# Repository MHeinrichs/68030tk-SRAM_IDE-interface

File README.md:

[This project moved to gitlab on the day M$ bought github](https://gitlab.com/MHeinrichs/68030tk-SRAM_IDE-interface)

The new repository is at: https://gitlab.com/MHeinrichs/68030tk-SRAM_IDE-interface

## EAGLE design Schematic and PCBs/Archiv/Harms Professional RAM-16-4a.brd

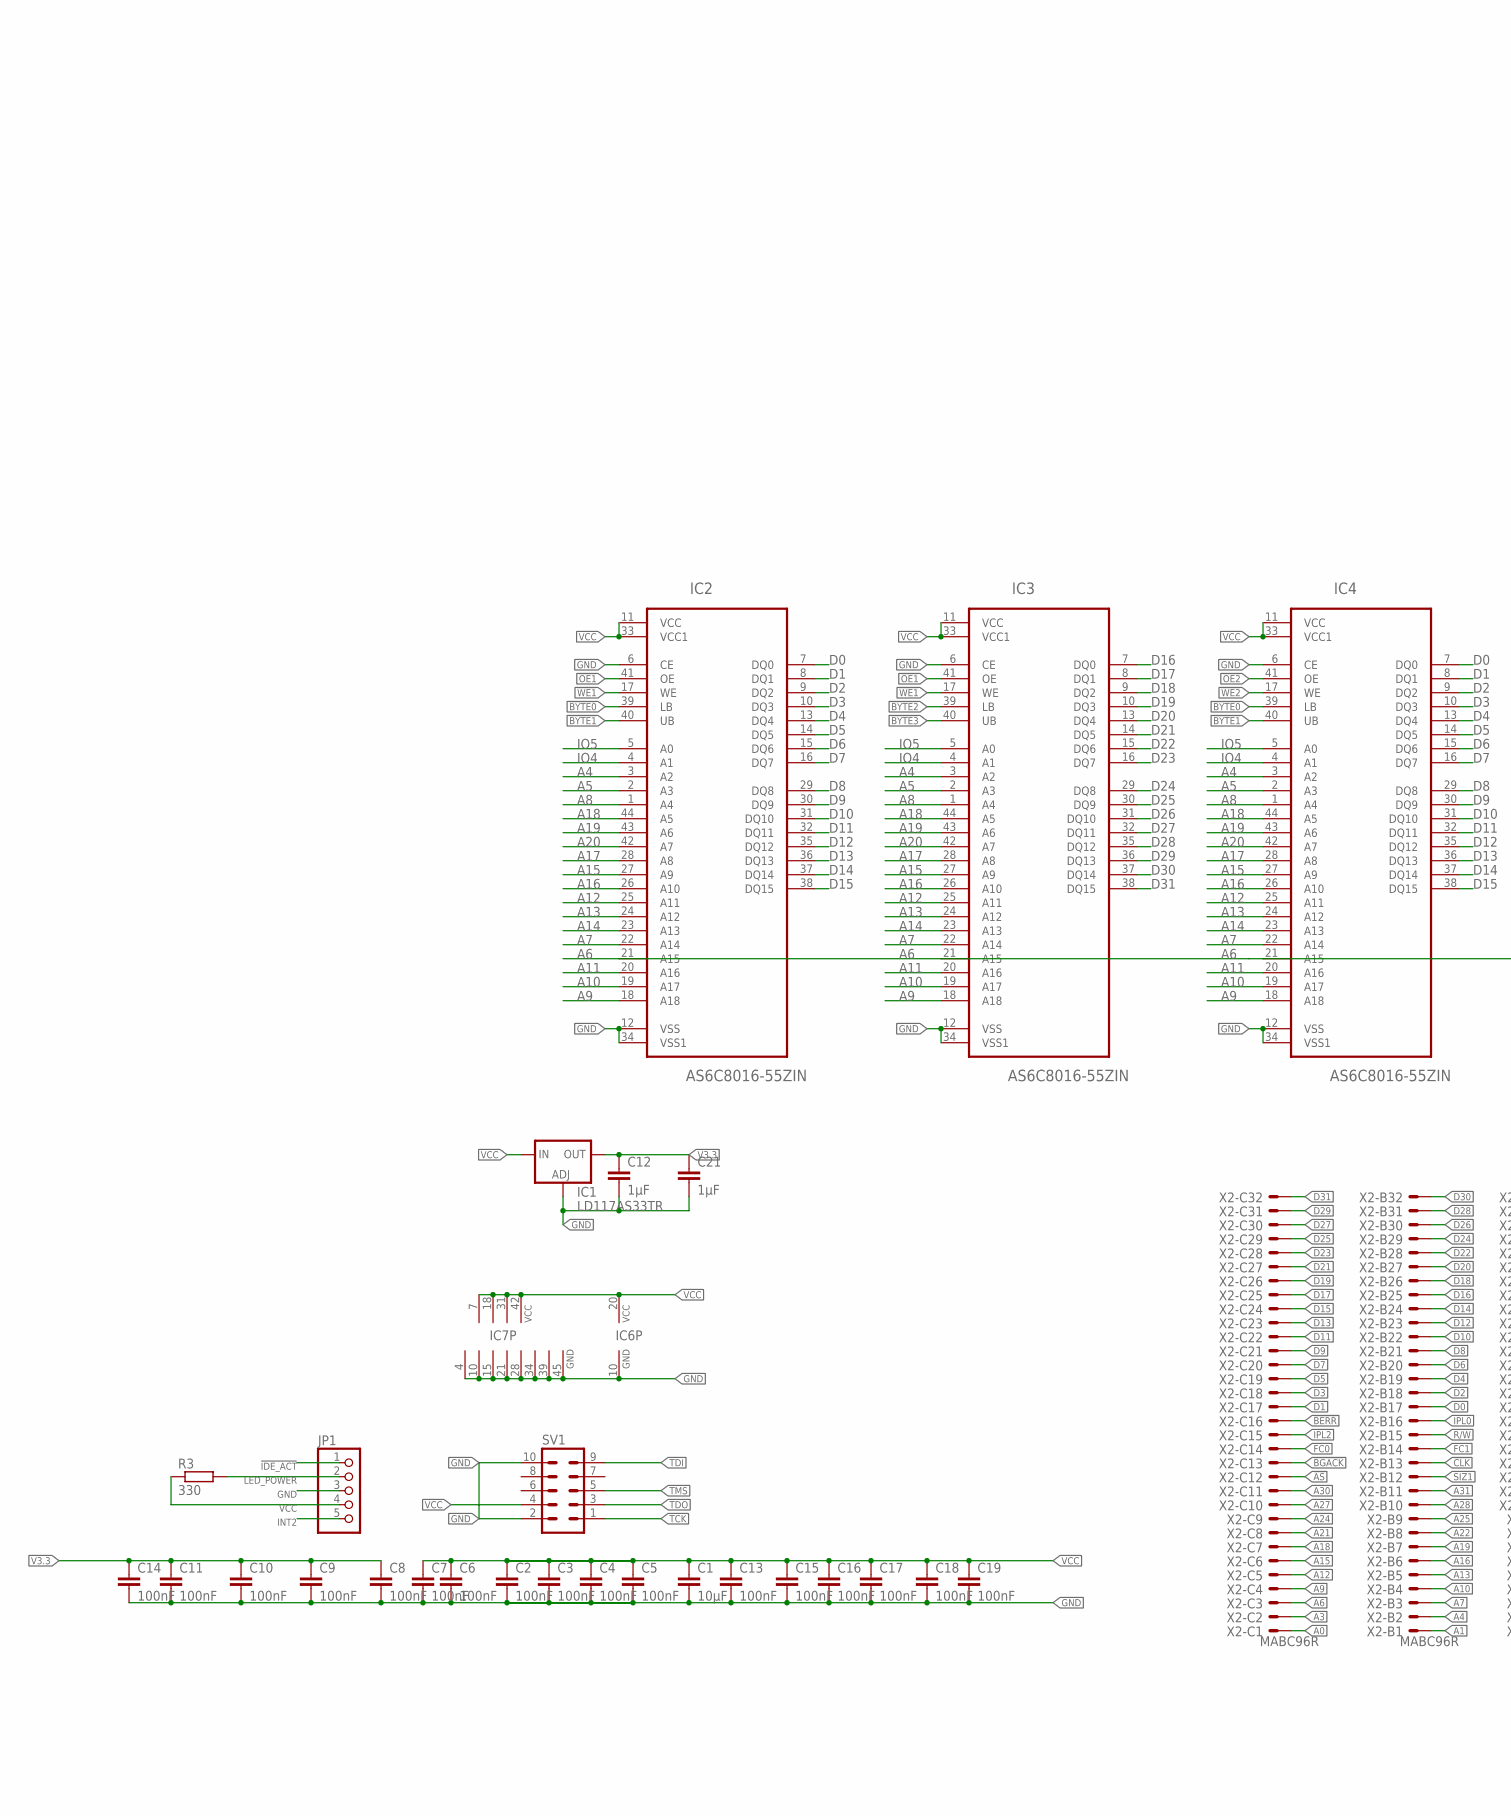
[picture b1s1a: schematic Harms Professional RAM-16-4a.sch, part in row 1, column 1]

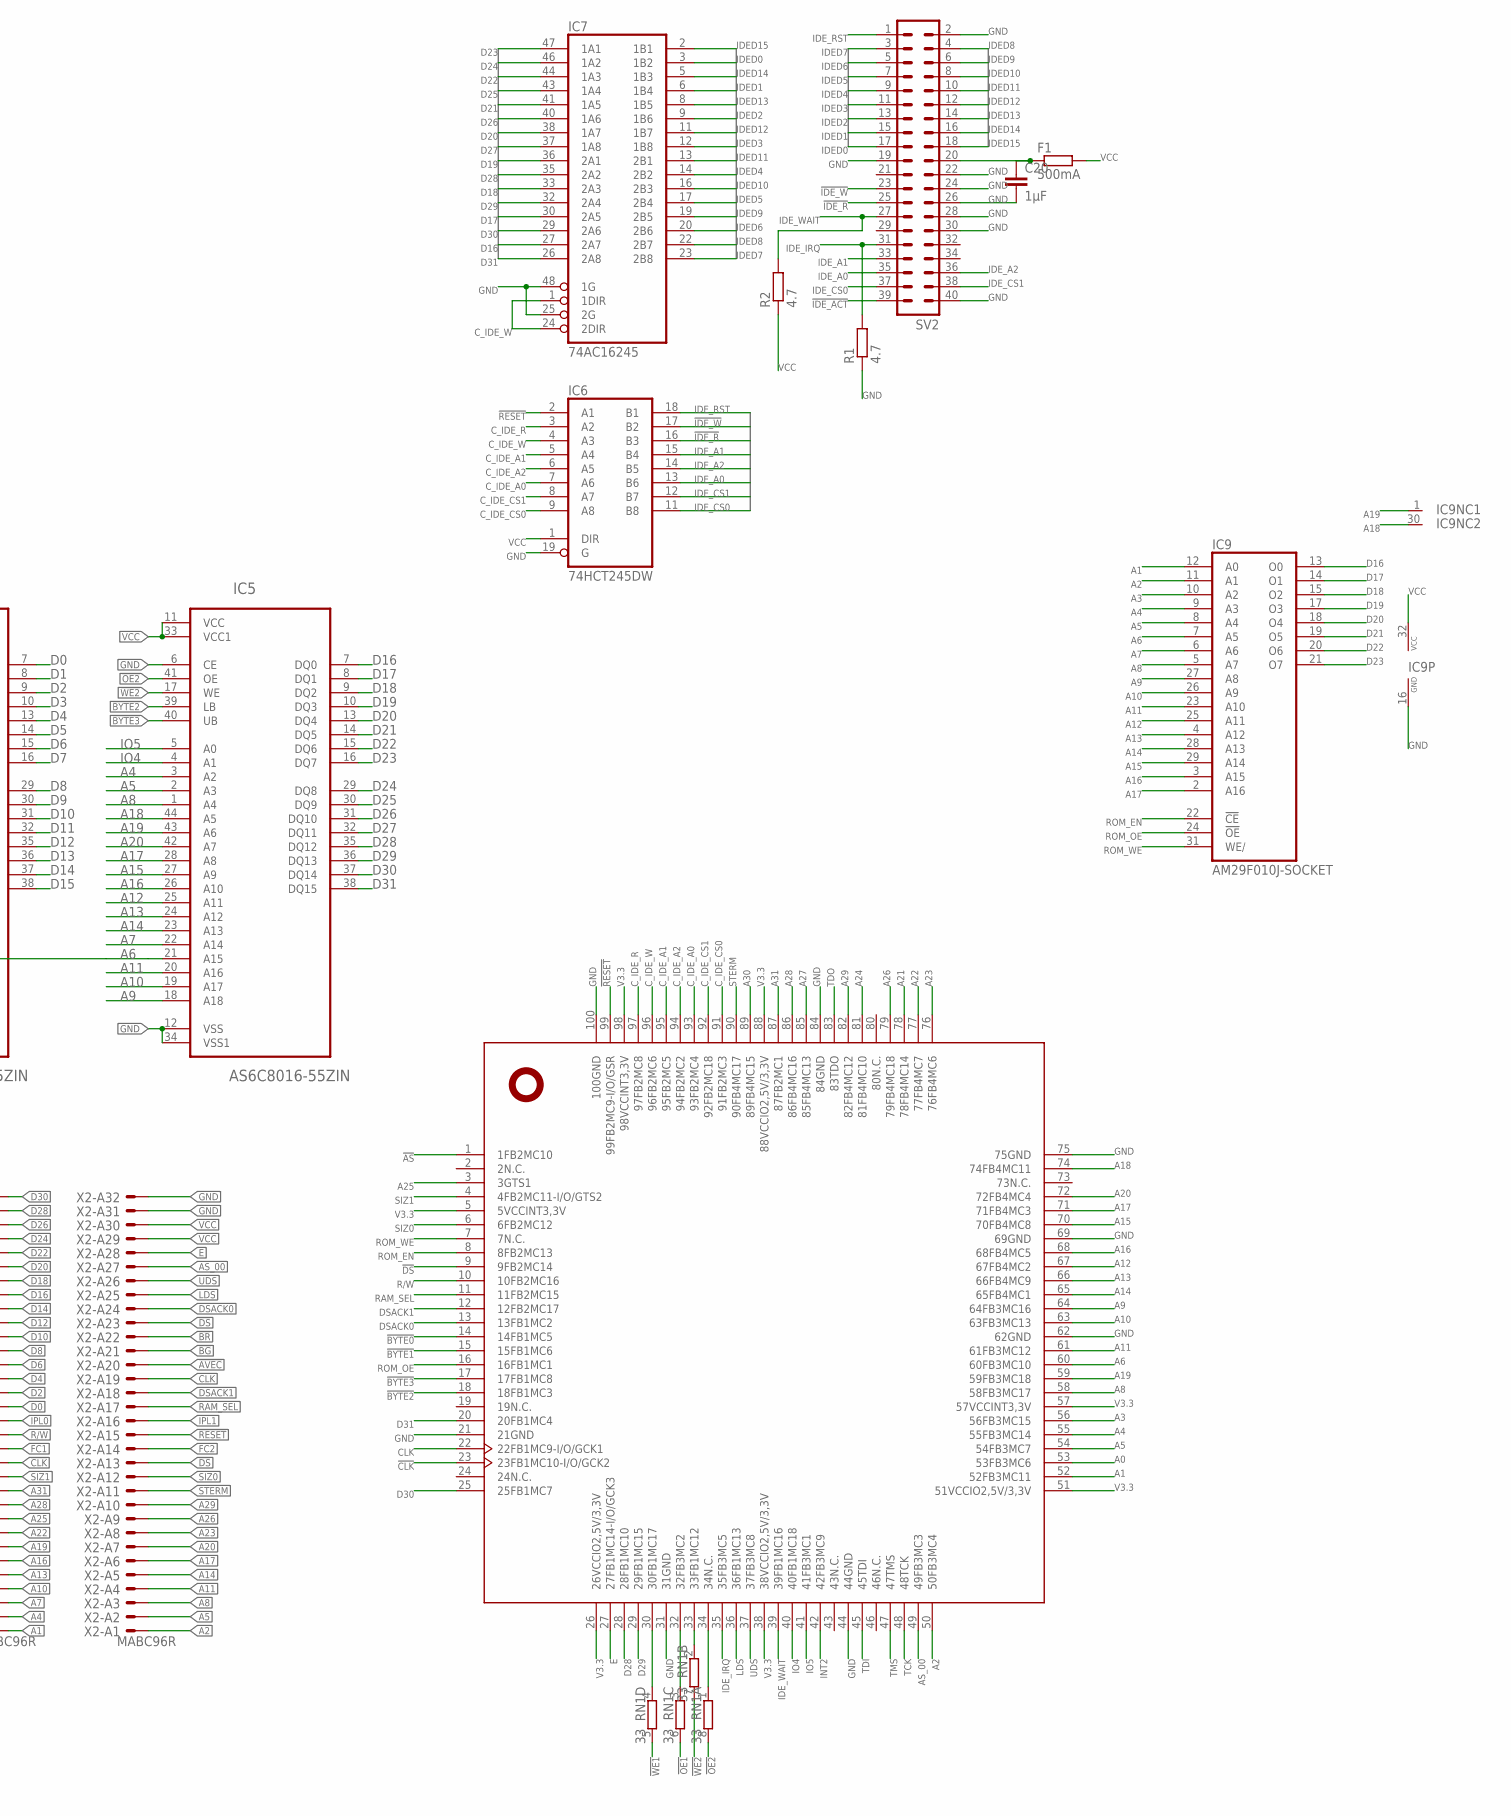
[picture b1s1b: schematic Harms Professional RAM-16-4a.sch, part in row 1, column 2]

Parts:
C1: 10µF; C0805K
C2, C3, C4, C5, C6, C7, C8, C9, C10, C11, C13, C14, C15, C16, C17, C18, C19: 100nF; C0603K
C12, C20, C21: 1µF; C0805K
F1: 500mA; R2512
IC1: LD117AS33TR; SOT223
IC2, IC3, IC4, IC5: AS6C8016-55ZIN; TSOP-2_44
IC6: 74HCT245DW; SO20W
IC7: 74AC16245; SSOP48DL
IC9: AM29F010J-SOCKET; PLCC-32-SMT-TT
IC10: XC9572XLTQ100; TQ100
JP1: PINHD-1X5; 1X05
R1, R2: 4.7; R0603
R3: 330; R0603
RN1: 33; CAY16
SV1: ML10
SV2: ML40
X2: MABC96R

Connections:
!AS: IC10.1 (1FB2MC10), X2.C12
!AVEC: X2.A20
!BERR: X2.C16
!BG: X2.A21
!BGACK: X2.C13
!BR: X2.A22
!BYTE0: IC2.39 (LB), IC4.39 (LB), IC10.14 (14FB1MC5)
!BYTE1: IC2.40 (UB), IC4.40 (UB), IC10.15 (15FB1MC6)
!BYTE2: IC3.39 (LB), IC5.39 (LB), IC10.18 (18FB1MC3)
!BYTE3: IC3.40 (UB), IC5.40 (UB), IC10.17 (17FB1MC8)
!CLK: IC10.23 (23FB1MC10-I/O/GCK2), X2.B13
!DS: IC10.9 (9FB2MC14), X2.A13, X2.A23
!IDE_ACT: JP1.1, SV2.39
!IDE_R: IC6.16 (B3), SV2.25
!IDE_W: IC6.17 (B2), SV2.23
!OE1: IC2.41 (OE), IC3.41 (OE), RN1.6 (2)
!OE2: IC4.41 (OE), IC5.41 (OE), RN1.8 (2)
!RESET: IC6.2 (A1), IC10.99 (99FB2MC9-I/O/GSR), X2.A15
!WE1: IC2.17 (WE), IC3.17 (WE), RN1.5 (2)
!WE2: IC4.17 (WE), IC5.17 (WE), RN1.7 (2)
A0: IC10.53 (53FB3MC6), X2.C1
A1: IC9.12 (A0), IC10.52 (52FB3MC11), X2.B1
A2: IC9.11 (A1), IC10.50 (50FB3MC4), X2.A1
A3: IC9.10 (A2), IC10.56 (56FB3MC15), X2.C2
A4: IC2.3 (A2), IC3.3 (A2), IC4.3 (A2), IC5.3 (A2), IC9.9 (A3), IC10.55 (55FB3MC14), X2.B2
A5: IC2.2 (A3), IC3.2 (A3), IC4.2 (A3), IC5.2 (A3), IC9.8 (A4), IC10.54 (54FB3MC7), X2.A2
A6: IC2.21 (A15), IC3.21 (A15), IC4.21 (A15), IC5.21 (A15), IC9.7 (A5), IC10.60 (60FB3MC10), X2.C3
A7: IC2.22 (A14), IC3.22 (A14), IC4.22 (A14), IC5.22 (A14), IC9.6 (A6), X2.B3
A8: IC2.1 (A4), IC3.1 (A4), IC4.1 (A4), IC5.1 (A4), IC9.5 (A7), IC10.58 (58FB3MC17), X2.A3
A9: IC2.18 (A18), IC3.18 (A18), IC4.18 (A18), IC5.18 (A18), IC9.27 (A8), IC10.64 (64FB3MC16), X2.C4
A10: IC2.19 (A17), IC3.19 (A17), IC4.19 (A17), IC5.19 (A17), IC9.26 (A9), IC10.63 (63FB3MC13), X2.B4
A11: IC2.20 (A16), IC3.20 (A16), IC4.20 (A16), IC5.20 (A16), IC9.23 (A10), IC10.61 (61FB3MC12), X2.A4
A12: IC2.25 (A11), IC3.25 (A11), IC4.25 (A11), IC5.25 (A11), IC9.25 (A11), IC10.67 (67FB4MC2), X2.C5
A13: IC2.24 (A12), IC3.24 (A12), IC4.24 (A12), IC5.24 (A12), IC9.4 (A12), IC10.66 (66FB4MC9), X2.B5
A14: IC2.23 (A13), IC3.23 (A13), IC4.23 (A13), IC5.23 (A13), IC9.28 (A13), IC10.65 (65FB4MC1), X2.A5
A15: IC2.27 (A9), IC3.27 (A9), IC4.27 (A9), IC5.27 (A9), IC9.29 (A14), IC10.70 (70FB4MC8), X2.C6
A16: IC2.26 (A10), IC3.26 (A10), IC4.26 (A10), IC5.26 (A10), IC9.3 (A15), IC10.68 (68FB4MC5), X2.B6
A17: IC2.28 (A8), IC3.28 (A8), IC4.28 (A8), IC5.28 (A8), IC9.2 (A16), IC10.71 (71FB4MC3), X2.A6
A18: IC2.44 (A5), IC3.44 (A5), IC4.44 (A5), IC5.44 (A5), IC9.30 (NC), IC10.74 (74FB4MC11), X2.C7
A19: IC2.43 (A6), IC3.43 (A6), IC4.43 (A6), IC5.43 (A6), IC9.1 (NC), IC10.59 (59FB3MC18), X2.B7
A20: IC2.42 (A7), IC3.42 (A7), IC4.42 (A7), IC5.42 (A7), IC10.72 (72FB4MC4), X2.A7
A21: IC10.78 (78FB4MC14), X2.C8
A22: IC10.77 (77FB4MC7), X2.B8
A23: IC10.76 (76FB4MC6), X2.A8
A24: IC10.81 (81FB4MC10), X2.C9
A25: IC10.3 (3GTS1), X2.B9
A26: IC10.79 (79FB4MC18), X2.A9
A27: IC10.85 (85FB4MC13), X2.C10
A28: IC10.86 (86FB4MC16), X2.B10
A29: IC10.82 (82FB4MC12), X2.A10
A30: IC10.89 (89FB4MC15), X2.C11
A31: IC10.87 (87FB2MC1), X2.B11
AS_00: IC10.49 (49FB3MC3), X2.A27
CLK: IC10.22 (22FB1MC9-I/O/GCK1), X2.A19
C_IDE_A0: IC6.7 (A6), IC10.93 (93FB2MC4)
C_IDE_A1: IC6.5 (A4), IC10.95 (95FB2MC5)
C_IDE_A2: IC6.6 (A5), IC10.94 (94FB2MC2)
C_IDE_CS0: IC6.9 (A8), IC10.91 (91FB2MC3)
C_IDE_CS1: IC6.8 (A7), IC10.92 (92FB2MC18)
C_IDE_R: IC6.3 (A2), IC10.97 (97FB2MC8)
C_IDE_W: IC6.4 (A3), IC7.1 (1DIR), IC7.24 (2DIR), IC10.96 (96FB2MC6)
D0: IC2.7 (DQ0), IC4.7 (DQ0), X2.B17
D1: IC2.8 (DQ1), IC4.8 (DQ1), X2.C17
D2: IC2.9 (DQ2), IC4.9 (DQ2), X2.B18
D3: IC2.10 (DQ3), IC4.10 (DQ3), X2.C18
D4: IC2.13 (DQ4), IC4.13 (DQ4), X2.B19
D5: IC2.14 (DQ5), IC4.14 (DQ5), X2.C19
D6: IC2.15 (DQ6), IC4.15 (DQ6), X2.B20
D7: IC2.16 (DQ7), IC4.16 (DQ7), X2.C20
D8: IC2.29 (DQ8), IC4.29 (DQ8), X2.B21
D9: IC2.30 (DQ9), IC4.30 (DQ9), X2.C21
D10: IC2.31 (DQ10), IC4.31 (DQ10), X2.B22
D11: IC2.32 (DQ11), IC4.32 (DQ11), X2.C22
D12: IC2.35 (DQ12), IC4.35 (DQ12), X2.B23
D13: IC2.36 (DQ13), IC4.36 (DQ13), X2.C23
D14: IC2.37 (DQ14), IC4.37 (DQ14), X2.B24
D15: IC2.38 (DQ15), IC4.38 (DQ15), X2.C24
D16: IC3.7 (DQ0), IC5.7 (DQ0), IC7.27 (2A7), IC9.13 (O0), X2.B25
D17: IC3.8 (DQ1), IC5.8 (DQ1), IC7.30 (2A5), IC9.14 (O1), X2.C25
D18: IC3.9 (DQ2), IC5.9 (DQ2), IC7.33 (2A3), IC9.15 (O2), X2.B26
D19: IC3.10 (DQ3), IC5.10 (DQ3), IC7.36 (2A1), IC9.17 (O3), X2.C26
D20: IC3.13 (DQ4), IC5.13 (DQ4), IC7.38 (1A7), IC9.18 (O4), X2.B27
D21: IC3.14 (DQ5), IC5.14 (DQ5), IC7.41 (1A5), IC9.19 (O5), X2.C27
D22: IC3.15 (DQ6), IC5.15 (DQ6), IC7.44 (1A3), IC9.20 (O6), X2.B28
D23: IC3.16 (DQ7), IC5.16 (DQ7), IC7.47 (1A1), IC9.21 (O7), X2.C28
D24: IC3.29 (DQ8), IC5.29 (DQ8), IC7.46 (1A2), X2.B29
D25: IC3.30 (DQ9), IC5.30 (DQ9), IC7.43 (1A4), X2.C29
D26: IC3.31 (DQ10), IC5.31 (DQ10), IC7.40 (1A6), X2.B30
D27: IC3.32 (DQ11), IC5.32 (DQ11), IC7.37 (1A8), X2.C30
D28: IC3.35 (DQ12), IC5.35 (DQ12), IC7.35 (2A2), IC10.28 (28FB1MC10), X2.B31
D29: IC3.36 (DQ13), IC5.36 (DQ13), IC7.32 (2A4), IC10.29 (29FB1MC15), X2.C31
D30: IC3.37 (DQ14), IC5.37 (DQ14), IC7.29 (2A6), IC10.25 (25FB1MC7), X2.B32
D31: IC3.38 (DQ15), IC5.38 (DQ15), IC7.26 (2A8), IC10.20 (20FB1MC4), X2.C32
DSACK0: IC10.13 (13FB1MC2), X2.A24
DSACK1: IC10.12 (12FB2MC17), X2.A18
E: IC10.27 (27FB1MC14-I/O/GCK3), X2.A28
FC0: X2.C14
FC1: X2.B14
FC2: X2.A14
GND: C1.2, C2.2, C3.2, C4.2, C5.2, C6.2, C7.2, C8.2, C9.2, C10.2, C11.2, C12.2, C13.2, C14.2, C15.2, C16.2, C17.2, C18.2, C19.2, C20.2, C21.2, IC1.1 (ADJ), IC2.6 (CE), IC2.12 (VSS), IC2.34 (VSS1), IC3.6 (CE), IC3.12 (VSS), IC3.34 (VSS1), IC4.6 (CE), IC4.12 (VSS), IC4.34 (VSS1), IC5.6 (CE), IC5.12 (VSS), IC5.34 (VSS1), IC6.10 (GND), IC6.19 (G), IC7.4 (GND), IC7.10 (GND), IC7.15 (GND), IC7.21 (GND), IC7.25 (2G), IC7.28 (GND), IC7.34 (GND), IC7.39 (GND), IC7.45 (GND), IC7.48 (1G), IC9.16 (GND), IC10.21 (21GND), IC10.31 (31GND), IC10.44 (44GND), IC10.62 (62GND), IC10.69 (69GND), IC10.75 (75GND), IC10.84 (84GND), IC10.100 (100GND), JP1.3, R1.1, SV1.2, SV1.10, SV2.2, SV2.19, SV2.22, SV2.24, SV2.26, SV2.28, SV2.30, SV2.40, X2.A31, X2.A32
IDED0: IC7.3 (1B2), SV2.17
IDED1: IC7.6 (1B4), SV2.15
IDED2: IC7.9 (1B6), SV2.13
IDED3: IC7.12 (1B8), SV2.11
IDED4: IC7.14 (2B2), SV2.9
IDED5: IC7.17 (2B4), SV2.7
IDED6: IC7.20 (2B6), SV2.5
IDED7: IC7.23 (2B8), SV2.3
IDED8: IC7.22 (2B7), SV2.4
IDED9: IC7.19 (2B5), SV2.6
IDED10: IC7.16 (2B3), SV2.8
IDED11: IC7.13 (2B1), SV2.10
IDED12: IC7.11 (1B7), SV2.12
IDED13: IC7.8 (1B5), SV2.14
IDED14: IC7.5 (1B3), SV2.16
IDED15: IC7.2 (1B1), SV2.18
IDE_A0: IC6.13 (B6), SV2.35
IDE_A1: IC6.15 (B4), SV2.33
IDE_A2: IC6.14 (B5), SV2.36
IDE_CS0: IC6.11 (B8), SV2.37
IDE_CS1: IC6.12 (B7), SV2.38
IDE_IRQ: IC10.35 (35FB3MC5), R1.2, SV2.31
IDE_RST: IC6.18 (B1), SV2.1
IDE_WAIT: IC10.39 (39FB1MC16), R2.2, SV2.27
INT2: IC10.42 (42FB3MC9), JP1.5
IO4: IC2.4 (A1), IC3.4 (A1), IC4.4 (A1), IC5.4 (A1), IC10.40 (40FB1MC18)
IO5: IC2.5 (A0), IC3.5 (A0), IC4.5 (A0), IC5.5 (A0), IC10.41 (41FB3MC1)
IPL0: X2.B16
IPL1: X2.A16
IPL2: X2.C15
KEY_PIN_POWER: C20.1, F1.1, SV2.20
LDS: IC10.36 (36FB1MC13), X2.A25
LED_POWER: JP1.2, R3.2
unnamed: IC10.30 (30FB1MC17), RN1.4 (1)
unnamed: IC10.34 (34N.C.), RN1.1
unnamed: IC10.33 (33FB1MC12), RN1.2 (1)
unnamed: IC10.32 (32FB3MC2), RN1.3 (1)
R/W: IC10.10 (10FB2MC16), X2.B15
RAM_SEL: IC10.11 (11FB2MC15), X2.A17
ROM_EN: IC9.22 (!CE), IC10.8 (8FB2MC13)
ROM_OE: IC9.24 (!OE), IC10.16 (16FB1MC1)
ROM_WE: IC9.31 (WE/), IC10.7 (7N.C.)
SIZ0: IC10.6 (6FB2MC12), X2.A12
SIZ1: IC10.4 (4FB2MC11-I/O/GTS2), X2.B12
STERM: IC10.90 (90FB4MC17), X2.A11
TCK: IC10.48 (48TCK), SV1.1
TDI: IC10.45 (45TDI), SV1.9
TDO: IC10.83 (83TDO), SV1.3
TMS: IC10.47 (47TMS), SV1.5
UDS: IC10.37 (37FB3MC8), X2.A26
V3.3: C8.1, C9.1, C10.1, C11.1, C12.1, C14.1, C21.1, IC1.4 (OUT), IC10.5 (5VCCINT3,3V), IC10.26 (26VCCIO2,5V/3,3V), IC10.38 (38VCCIO2,5V/3,3V), IC10.51 (51VCCIO2,5V/3,3V), IC10.57 (57VCCINT3,3V), IC10.88 (88VCCIO2,5V/3,3V), IC10.98 (98VCCINT3,3V)
VCC: C1.1, C2.1, C3.1, C4.1, C5.1, C6.1, C7.1, C13.1, C15.1, C16.1, C17.1, C18.1, C19.1, F1.2, IC1.3 (IN), IC2.11 (VCC), IC2.33 (VCC1), IC3.11 (VCC), IC3.33 (VCC1), IC4.11 (VCC), IC4.33 (VCC1), IC5.11 (VCC), IC5.33 (VCC1), IC6.1 (DIR), IC6.20 (VCC), IC7.7 (VCC), IC7.18 (VCC), IC7.31 (VCC), IC7.42 (VCC), IC9.32 (VCC), JP1.4, R2.1, R3.1, SV1.4, X2.A29, X2.A30

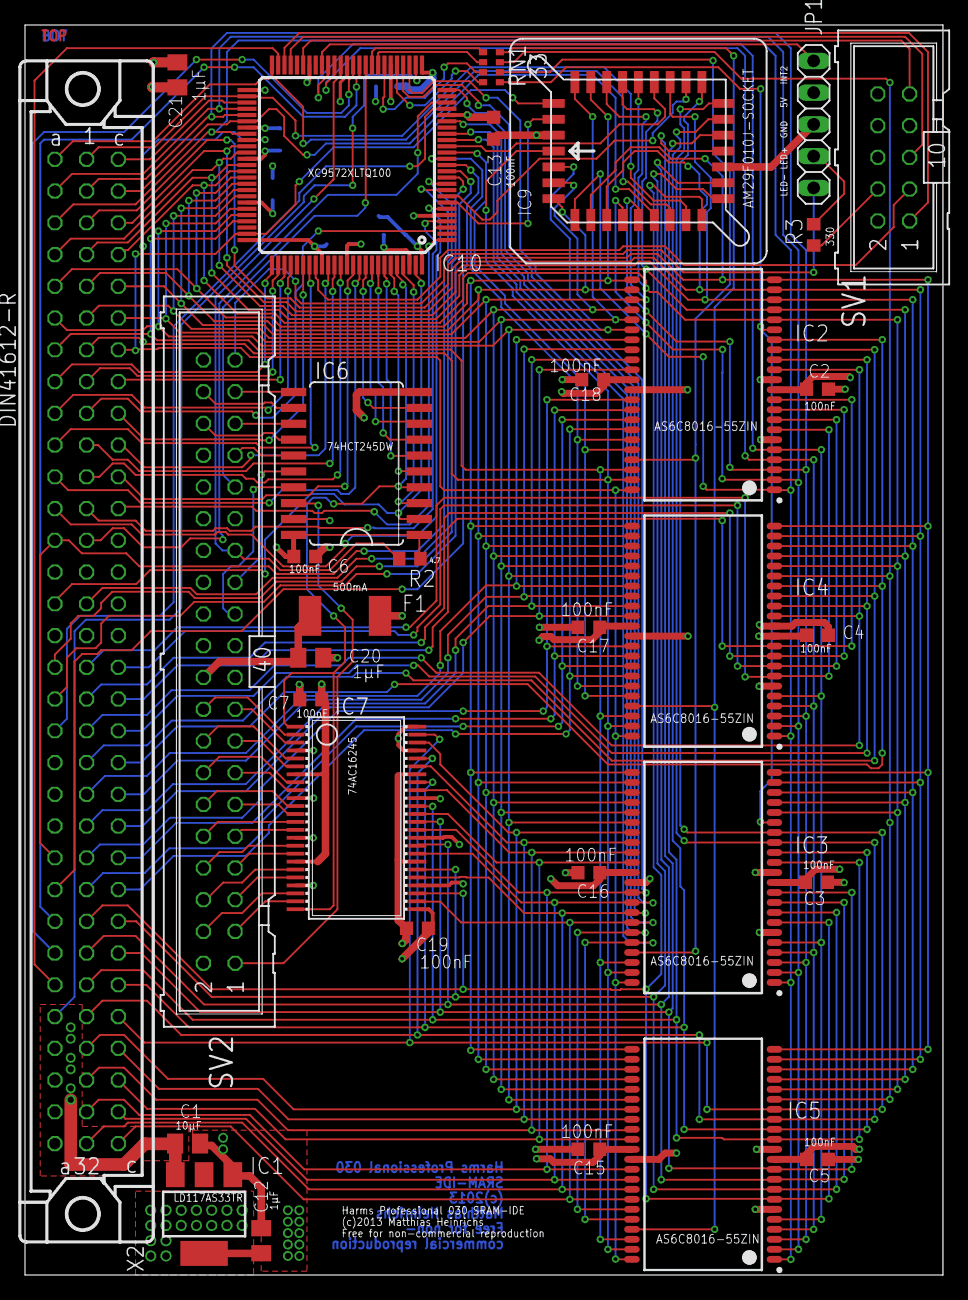
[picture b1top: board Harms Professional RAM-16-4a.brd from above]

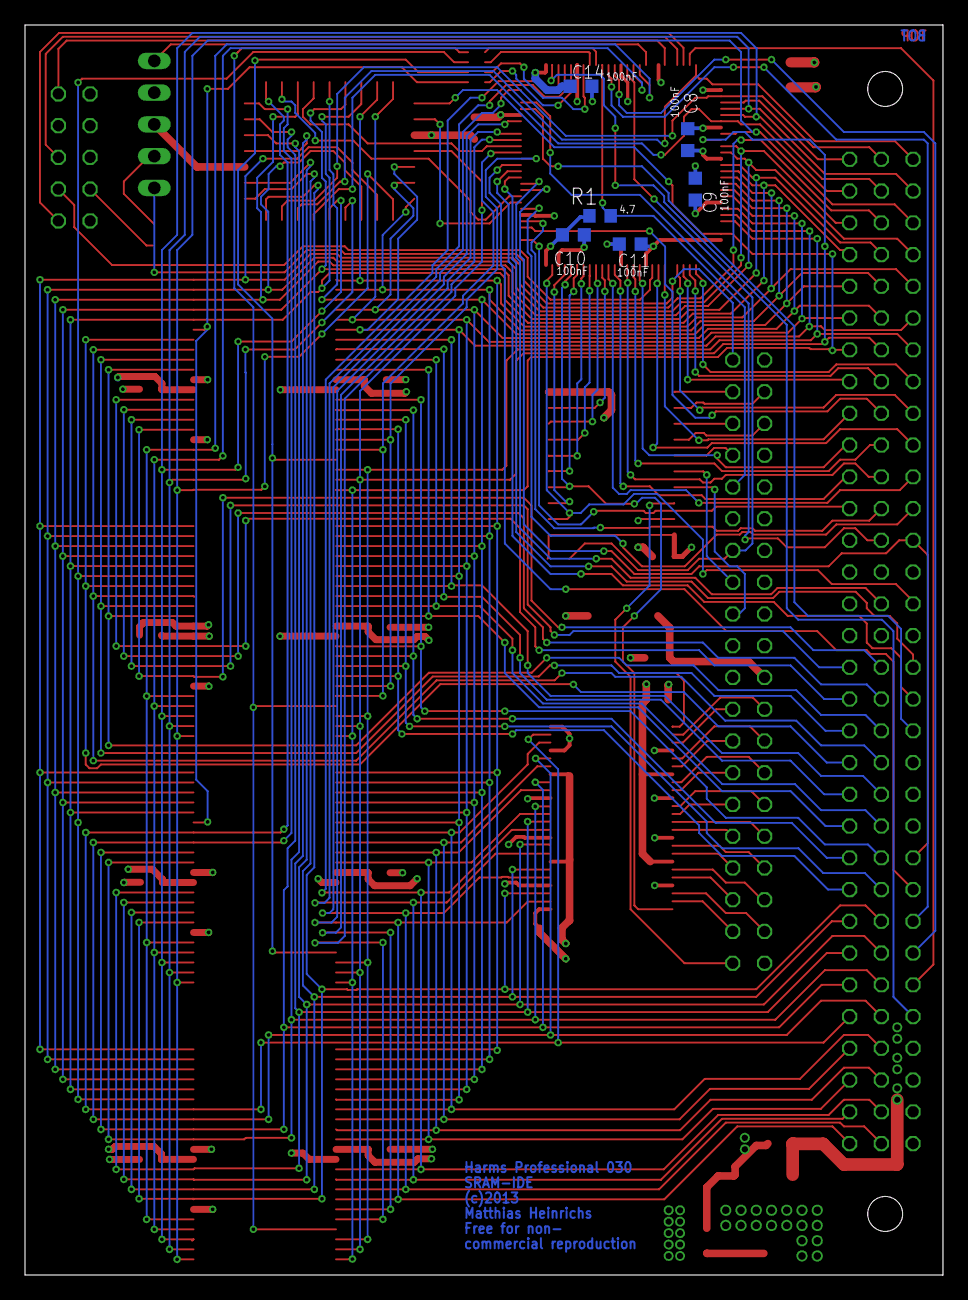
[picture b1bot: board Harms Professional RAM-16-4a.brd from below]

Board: 4 copper layers, 73.4 x 100.0 mm, 39 parts (6 on the bottom side), 141 nets.

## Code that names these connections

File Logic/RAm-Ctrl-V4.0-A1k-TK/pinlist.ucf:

#PIN MAP for the Harms Professional RAM Controller
NET reset LOC = "P99";
NET "IDE_W" LOC = "P97";
NET "IDE_R" LOC = "P96";
NET "IDE_A[1]" LOC = "P95";
NET "IDE_A[2]" LOC = "P94";
NET "IDE_A[0]" LOC = "P93";
NET "IDE_CS[1]" LOC = "P92";
NET "IDE_CS[0]" LOC = "P91";
NET "STERM" LOC = "P90";
NET "A[30]" LOC = "P89";
NET "A[31]" LOC = "P87";
NET "A[28]" LOC = "P86";
NET "A[27]" LOC = "P85";
NET "A[29]" LOC = "P82";
NET "A[24]" LOC = "P81";
NET "A[26]" LOC = "P79";
NET "A[21]" LOC = "P78";
NET "A[22]" LOC = "P77";
NET "A[23]" LOC = "P76";
NET "A[18]" LOC = "P74";
NET "A[20]" LOC = "P72";
NET "A[17]" LOC = "P71";
NET "A[15]" LOC = "P70";
NET "A[16]" LOC = "P68";
NET "A[12]" LOC = "P67";
NET "A[13]" LOC = "P66";
NET "A[14]" LOC = "P65";
NET "A[9]" LOC = "P64";
NET "A[10]" LOC = "P63";
NET "A[11]" LOC = "P61";
NET "A[6]" LOC = "P60";
NET "A[19]" LOC = "P59";
NET "A[8]" LOC = "P58";
NET "A[3]" LOC = "P56";
NET "A[4]" LOC = "P55";
NET "A[5]" LOC = "P54";
NET "A[0]" LOC = "P53";
NET "A[1]" LOC = "P52";
NET "A[2]" LOC = "P50";
NET "CIIN" LOC = "P49"; #this is AS_00 on the original HARMS-Board
NET "INT2" LOC = "P42";
NET "IO5" LOC = "P41";
NET "IO4" LOC = "P40";
NET "IDE_WAIT" LOC = "P39";
#NET "UDS" LOC = "P37";
#NET "LDS" LOC = "P36";
NET "IDE_IRQ" LOC = "P35";
NET "OE[1]" LOC = "P34";
NET "WE[1]" LOC = "P33";
NET "OE[0]" LOC = "P32";
NET "WE[0]" LOC = "P30";
NET "D[1]" LOC = "P29"; #Internal D1=external D29
NET "D[0]" LOC = "P28"; #Internal D0=external D28
#NET "E" LOC = "P27";
NET "D[2]" LOC = "P25"; #Internal D2=external D30
NET "ECS" LOC = "P23";
NET "clk" LOC = "P22";
NET "D[3]" LOC = "P20"; #Internal D3=external D31
NET "BYTE[2]" LOC = "P18";
NET "BYTE[3]" LOC = "P17";
NET "ROM_OE" LOC = "P16";
NET "BYTE[1]" LOC = "P15";
NET "BYTE[0]" LOC = "P14";
NET "DSACK[0]" LOC = "P13";
NET "DSACK[1]" LOC = "P12";
NET "nRAM_SEL" LOC = "P11";
NET "RW" LOC = "P10";
NET "nDS" LOC = "P9";
NET "ROM_EN" LOC = "P8";
NET "ROM_WE" LOC = "P7";
NET "SIZ[0]" LOC = "P6";
NET "SIZ[1]" LOC = "P4";
NET "A[25]" LOC = "P3";
NET "IDE_DIR" LOC = "P2";
NET "nAS" LOC = "P1";
#Created by Constraints Editor (xc95144xl-tq100-10) - 2015/02/08
NET "clk" TNM_NET = clk;
TIMESPEC TS_clk = PERIOD "clk" 50 MHz HIGH 50% INPUT_JITTER 100 ps;
#>DISABLED<#OFFSET = IN 2 ns VALID 10 ns BEFORE "clk" RISING;
#>DISABLED<#OFFSET = IN 2 ns VALID 10 ns BEFORE "clk" FALLING;
#Created by Constraints Editor (xc95144xl-tq100-10) - 2015/02/08
INST "A<0>" TNM = ADR;
INST "A<1>" TNM = ADR;
INST "A<2>" TNM = ADR;
INST "A<3>" TNM = ADR;
INST "A<4>" TNM = ADR;
INST "A<5>" TNM = ADR;
INST "A<6>" TNM = ADR;
INST "A<8>" TNM = ADR;
INST "A<9>" TNM = ADR;
INST "A<10>" TNM = ADR;
INST "A<11>" TNM = ADR;
INST "A<12>" TNM = ADR;
INST "A<13>" TNM = ADR;
INST "A<14>" TNM = ADR;
INST "A<15>" TNM = ADR;
INST "A<16>" TNM = ADR;
INST "A<17>" TNM = ADR;
INST "A<18>" TNM = ADR;
INST "A<19>" TNM = ADR;
INST "A<20>" TNM = ADR;
INST "A<21>" TNM = ADR;
INST "A<22>" TNM = ADR;
INST "A<23>" TNM = ADR;
INST "A<24>" TNM = ADR;
INST "A<25>" TNM = ADR;
INST "A<26>" TNM = ADR;
INST "A<27>" TNM = ADR;
INST "A<28>" TNM = ADR;
INST "A<29>" TNM = ADR;
INST "A<30>" TNM = ADR;
INST "A<31>" TNM = ADR;
INST "D<0>" TNM = DATA;
INST "D<1>" TNM = DATA;
INST "D<2>" TNM = DATA;
INST "D<3>" TNM = DATA;
#>DISABLED<#TIMEGRP "DATA" OFFSET = IN 14 ns VALID 20 ns BEFORE "clk" RISING;
INST "nAS" TNM = STROBES;
INST "nDS" TNM = STROBES;
INST "nAS" TNM = STROBES;
INST "nDS" TNM = STROBES;
INST "nAS" TNM = STROBES;
INST "nDS" TNM = STROBES;
#>DISABLED<#NET "nAS" OFFSET = IN 10 ns VALID 20 ns BEFORE "clk" RISING;
#>DISABLED<#NET "nDS" OFFSET = IN 10 ns VALID 20 ns BEFORE "clk" RISING;
INST "SIZ<0>" TNM = SIZE;
INST "SIZ<1>" TNM = SIZE;
INST "A<0>" TNM = ADR;
INST "A<1>" TNM = ADR;
INST "A<2>" TNM = ADR;
INST "A<3>" TNM = ADR;
INST "A<4>" TNM = ADR;
INST "A<5>" TNM = ADR;
INST "A<6>" TNM = ADR;
INST "A<8>" TNM = ADR;
INST "A<9>" TNM = ADR;
INST "A<10>" TNM = ADR;
INST "A<11>" TNM = ADR;
INST "A<12>" TNM = ADR;
INST "A<13>" TNM = ADR;
INST "A<14>" TNM = ADR;
INST "A<15>" TNM = ADR;
INST "A<16>" TNM = ADR;
INST "A<17>" TNM = ADR;
INST "A<18>" TNM = ADR;
INST "A<19>" TNM = ADR;
INST "A<20>" TNM = ADR;
INST "A<21>" TNM = ADR;
INST "A<22>" TNM = ADR;
INST "A<23>" TNM = ADR;
INST "A<24>" TNM = ADR;
INST "A<25>" TNM = ADR;
INST "A<26>" TNM = ADR;
INST "A<27>" TNM = ADR;
INST "A<28>" TNM = ADR;
INST "A<29>" TNM = ADR;
INST "A<30>" TNM = ADR;
INST "A<31>" TNM = ADR;
INST "SIZ<0>" TNM = ADR;
INST "SIZ<1>" TNM = ADR;
#>DISABLED<#TIMEGRP "ADR" OFFSET = IN 6 ns VALID 20 ns BEFORE "clk" FALLING;
INST "RW" TNM = RW;
#>DISABLED<#TIMEGRP "RW" OFFSET = IN 6 ns VALID 20 ns BEFORE "clk" FALLING;
#>DISABLED<#NET "ECS" OFFSET = IN 10 ns VALID 20 ns BEFORE "clk" FALLING;

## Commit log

2014-05-17 Initial Push
2014-05-18 Speed-adjustments for 33Mhz bus
2014-05-19 start for 50Mhz-Bus
2014-05-19 50MHz start
2014-05-19 clean up
2014-05-19 again: 50Mhz start
2014-05-21 just changes
2014-05-21 sync tests
2014-05-29 STERM working
2014-06-15 CIIN option added
2014-06-17 CIIN OPtion
2014-06-29 clocking IDE
2014-06-29 deleted temp folder
2014-06-29 IDE-Speed-UP and clocked design
2014-06-29 comments cleaned up
2014-08-09 WC Works
2014-08-09 Stable (up to now ;) )
2014-08-11 More Stable but no STERM :(
2014-08-26 Working @50MHz
2014-08-29 Switch to Xc95144XL
2014-09-06 50MHz RAM with 3WS
2014-10-03 4Ws but more satble
2014-10-04 3WS again!
2014-10-16 Cleaned up
2015-01-12 DMA-Working!
2015-02-08 New PCB4 LAyout
2015-02-09 Smal fix for LOOOONG writes
2015-02-19 Working with DMA and new layout
2015-03-28 Some Improvements
2015-06-26 MIsc Update
2015-11-29 Yeah! one wait state less!
2016-01-25 sync
2016-01-28 some files generated read data out prolonged
2016-06-02 Values corrected
2016-08-18 Horray! 0WS @50Mhz!
2016-08-24 Added CDTV-Support (25Mhz = 0WS)
2016-08-29 Switched to DSACK...
2016-09-28 Bugfix: IDE was cached! Eeek!
2016-10-06 v3.0 recompiled
2016-10-26 Updated some JEDs
2017-12-29 code clean up
2017-12-30 clean up completed and jeds generaterd
2019-08-28 Moved to gitlab

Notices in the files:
Schematic and PCBs/Archiv/Harms Professional RAM-16-4a.brd:
(c)2013
(c)2013 Matthias Heinrichs
